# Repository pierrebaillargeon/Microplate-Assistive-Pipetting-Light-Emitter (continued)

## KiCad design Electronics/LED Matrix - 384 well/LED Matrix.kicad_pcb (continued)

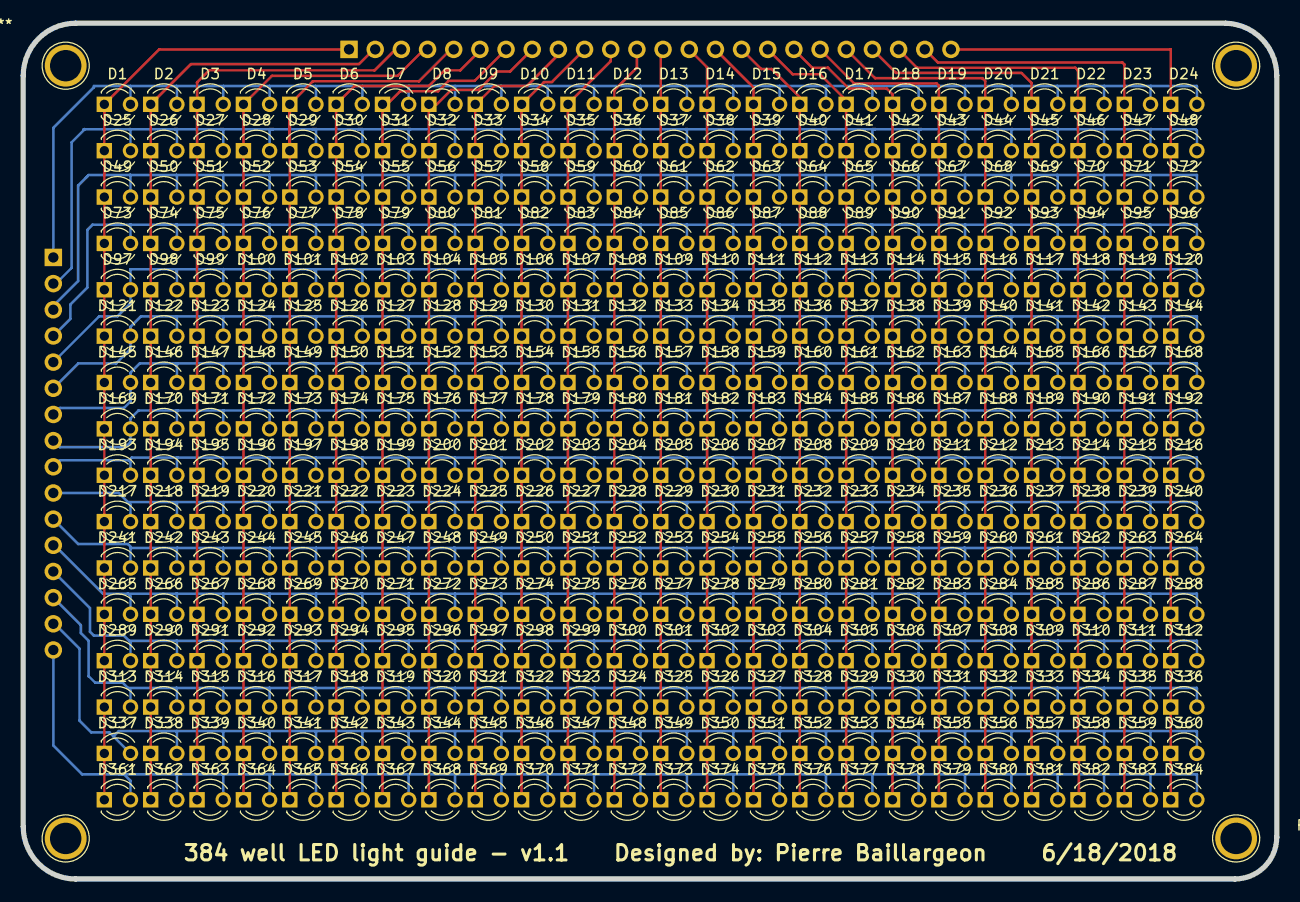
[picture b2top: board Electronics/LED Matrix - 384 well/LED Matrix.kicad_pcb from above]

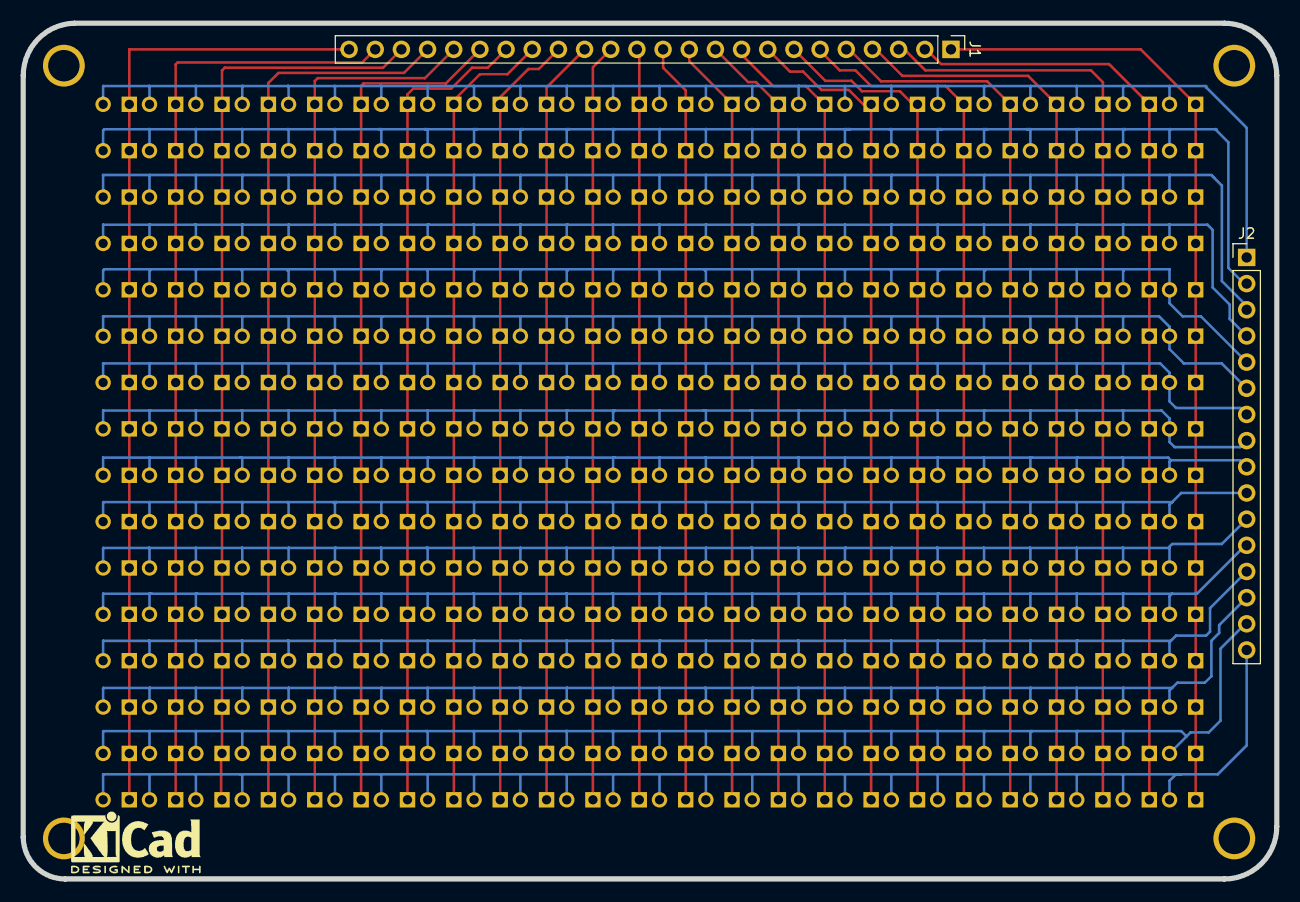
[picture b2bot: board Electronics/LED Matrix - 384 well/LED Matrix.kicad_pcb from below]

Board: 2 copper layers, 121.7 x 83.1 mm, 386 parts (2 on the bottom side), 40 nets.

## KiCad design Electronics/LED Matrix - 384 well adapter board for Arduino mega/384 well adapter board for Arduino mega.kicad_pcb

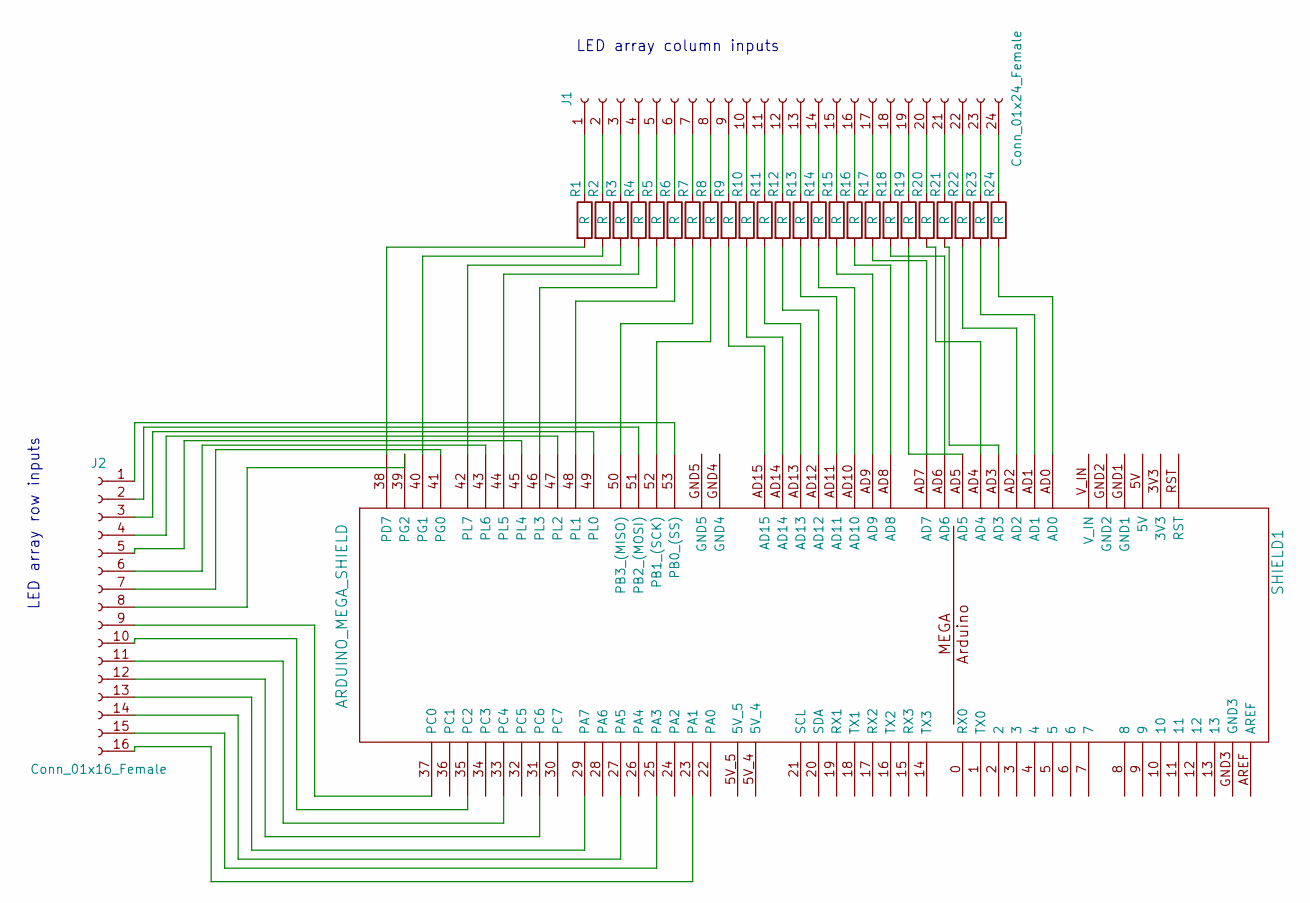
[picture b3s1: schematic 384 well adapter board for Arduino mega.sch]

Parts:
J1: Conn_01x24_Female; Socket_Strip_Straight_1x24_Pitch2.54mm
J2: Conn_01x16_Female; Socket_Strip_Straight_1x16_Pitch2.54mm
R1, R2, R3, R4, R5, R6, R7, R8, R9, R10, R11, R12, R13, R14, R15, R16, R17, R18, R19, R20, R21, R22, R23, R24: R; R_Axial_DIN0207_L6.3mm_D2.5mm_P7.62mm_Horizontal
SHIELD1: ARDUINO_MEGA_SHIELD; ARDUINO MEGA SHIELD

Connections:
unnamed: J1.1, R1.1
unnamed: J1.2, R2.1
unnamed: J1.3, R3.1
unnamed: J1.4, R4.1
unnamed: J1.5, R5.1
unnamed: J1.6, R6.1
unnamed: J1.7, R7.1
unnamed: J1.8, R8.1
unnamed: J1.9, R9.1
unnamed: J1.10, R10.1
unnamed: J1.11, R11.1
unnamed: J1.12, R12.1
unnamed: J1.13, R13.1
unnamed: J1.14, R14.1
unnamed: J1.15, R15.1
unnamed: J1.16, R16.1
unnamed: J1.17, R17.1
unnamed: J1.18, R18.1
unnamed: J1.19, R19.1
unnamed: J1.20, R20.1
unnamed: J1.21, R21.1
unnamed: J1.22, R22.1
unnamed: J1.23, R23.1
unnamed: J1.24, R24.1
unnamed: J2.1, SHIELD1.53 (PB0_(SS))
unnamed: J2.2, SHIELD1.51 (PB2_(MOSI))
unnamed: J2.3, SHIELD1.49 (PL0)
unnamed: J2.4, SHIELD1.47 (PL2)
unnamed: J2.5, SHIELD1.45 (PL4)
unnamed: J2.6, SHIELD1.43 (PL6)
unnamed: J2.7, SHIELD1.41 (PG0)
unnamed: J2.8, SHIELD1.39 (PG2)
unnamed: J2.9, SHIELD1.37 (PC0)
unnamed: J2.10, SHIELD1.35 (PC2)
unnamed: J2.11, SHIELD1.33 (PC4)
unnamed: J2.12, SHIELD1.31 (PC6)
unnamed: J2.13, SHIELD1.29 (PA7)
unnamed: J2.14, SHIELD1.27 (PA5)
unnamed: J2.15, SHIELD1.25 (PA3)
unnamed: J2.16, SHIELD1.23 (PA1)
unnamed: R1.2, SHIELD1.38 (PD7)
unnamed: R2.2, SHIELD1.40 (PG1)
unnamed: R3.2, SHIELD1.42 (PL7)
unnamed: R4.2, SHIELD1.44 (PL5)
unnamed: R5.2, SHIELD1.46 (PL3)
unnamed: R6.2, SHIELD1.48 (PL1)
unnamed: R7.2, SHIELD1.50 (PB3_(MISO))
unnamed: R8.2, SHIELD1.52 (PB1_(SCK))
unnamed: R9.2, SHIELD1.AD15
unnamed: R10.2, SHIELD1.AD14
unnamed: R11.2, SHIELD1.AD13
unnamed: R12.2, SHIELD1.AD12
unnamed: R13.2, SHIELD1.AD11
unnamed: R14.2, SHIELD1.AD10
unnamed: R15.2, SHIELD1.AD9
unnamed: R16.2, SHIELD1.AD8
unnamed: R17.2, SHIELD1.AD7
unnamed: R18.2, SHIELD1.AD6
unnamed: R19.2, SHIELD1.AD5
unnamed: R20.2, SHIELD1.AD4
unnamed: R21.2, SHIELD1.AD3
unnamed: R22.2, SHIELD1.AD2
unnamed: R23.2, SHIELD1.AD1
unnamed: R24.2, SHIELD1.AD0

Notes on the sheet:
LED array column inputs
LED array row inputs

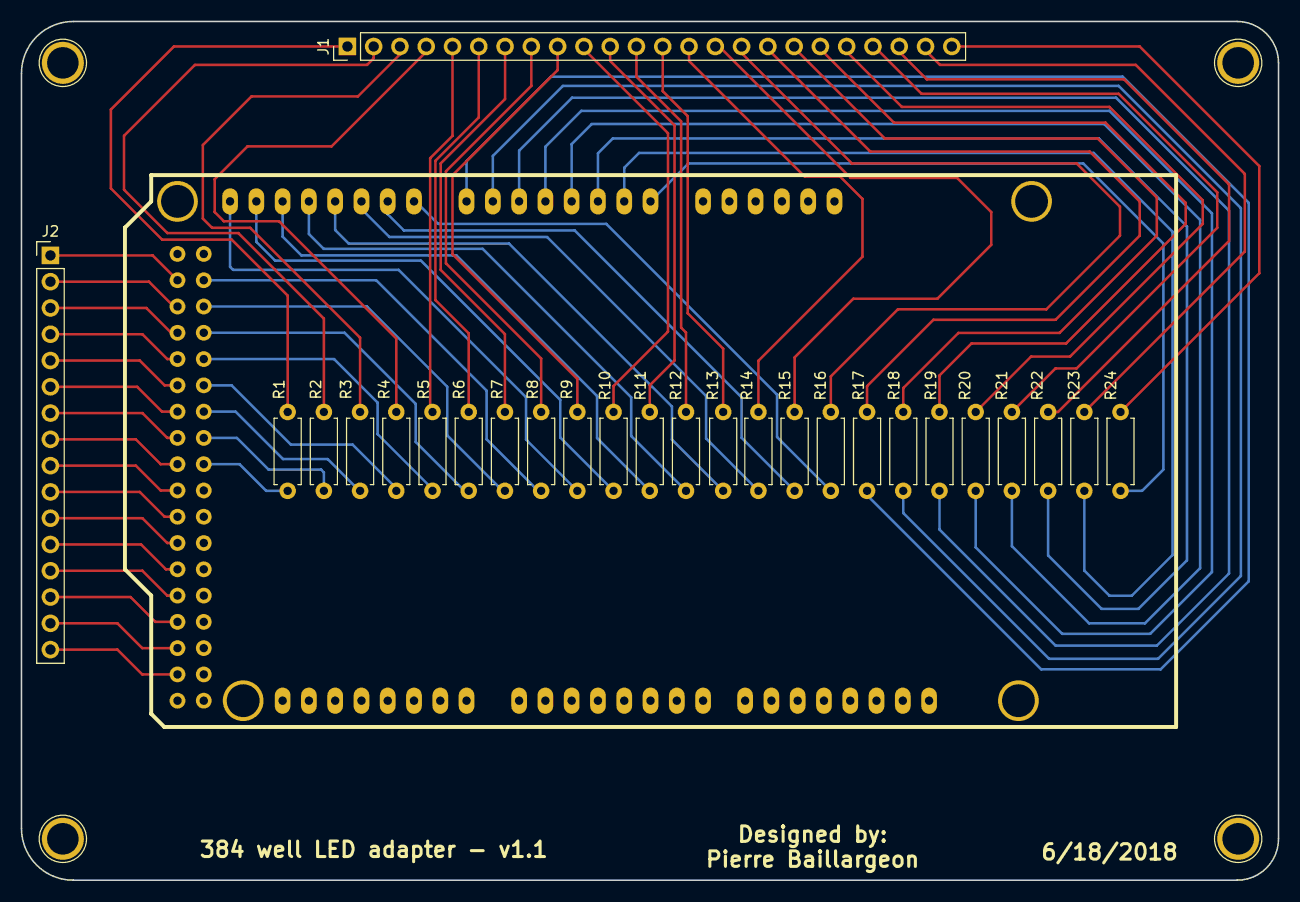
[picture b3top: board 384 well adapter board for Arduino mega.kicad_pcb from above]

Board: 2 copper layers, 121.5 x 83.0 mm, 27 parts (0 on the bottom side), 64 nets.

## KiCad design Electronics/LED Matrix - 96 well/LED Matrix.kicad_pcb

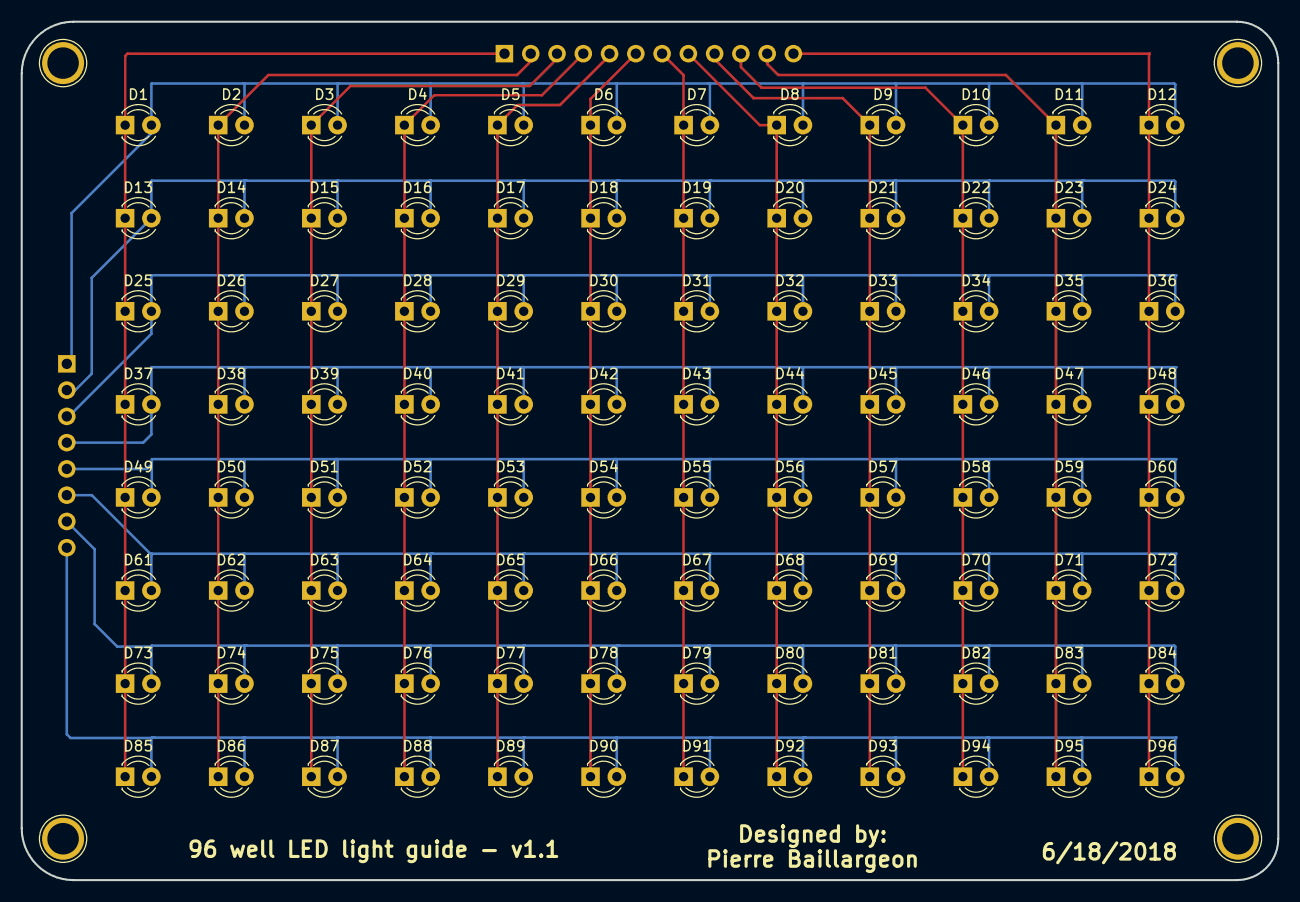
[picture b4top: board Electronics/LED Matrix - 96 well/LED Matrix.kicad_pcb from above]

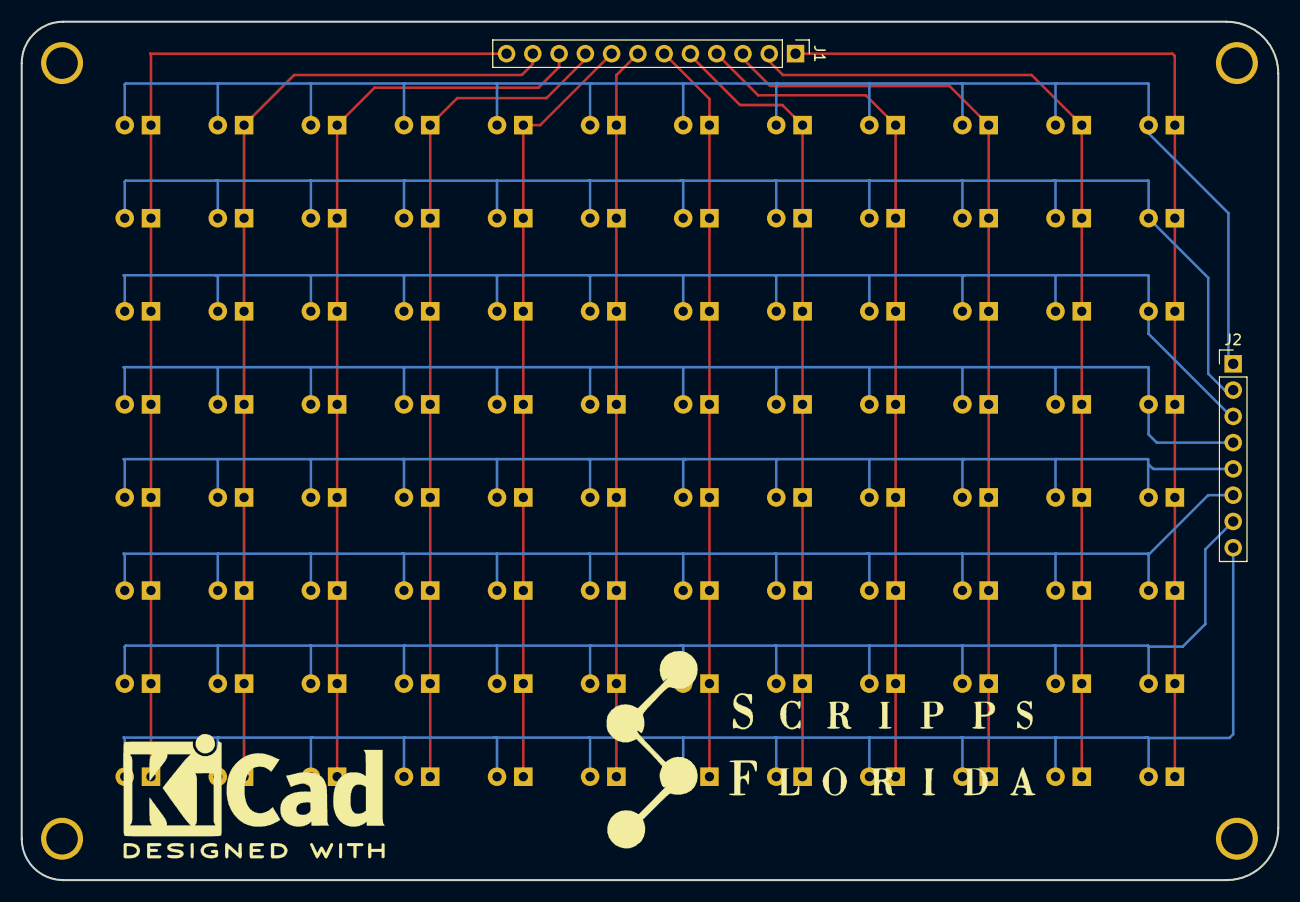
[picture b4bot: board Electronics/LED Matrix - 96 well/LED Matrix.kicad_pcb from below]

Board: 2 copper layers, 121.5 x 83.0 mm, 98 parts (2 on the bottom side), 20 nets.

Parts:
D1, D2, D3, D4, D5, D6, D7, D8, D9, D10, D11, D12, D13, D14, D15, D16, D17, D18, D19, D20, D21, D22, D23, D24, D25, D26, D27, D28, D29, D30, D31, D32, D33, D34, D35, D36, D37, D38, D39, D40, D41, D42, D43, D44, D45, D46, D47, D48, D49, D50, D51, D52, D53, D54, D55, D56, D57, D58, D59, D60, D61, D62, D63, D64, D65, D66, D67, D68, D69, D70, D71, D72, D73, D74, D75, D76, D77, D78, D79, D80, D81, D82, D83, D84, D85, D86, D87, D88, D89, D90, D91, D92, D93, D94, D95, D96: LED; LED_D3.0mm
J1: Conn_01x12_Male; Pin_Header_Straight_1x12_Pitch2.54mm
J2: Conn_01x08_Male; Pin_Header_Straight_1x08_Pitch2.54mm

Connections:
/1: D1.1, D13.1, D25.1, D37.1, D49.1, D61.1, D73.1, D85.1, J1.1
/2: D2.1, D14.1, D26.1, D38.1, D50.1, D62.1, D74.1, D86.1, J1.2
/3: D3.1, D15.1, D27.1, D39.1, D51.1, D63.1, D75.1, D87.1, J1.3
/4: D4.1, D16.1, D28.1, D40.1, D52.1, D64.1, D76.1, D88.1, J1.4
/5: D5.1, D17.1, D29.1, D41.1, D53.1, D65.1, D77.1, D89.1, J1.5
/6: D6.1, D18.1, D30.1, D42.1, D54.1, D66.1, D78.1, D90.1, J1.6
/7: D7.1, D19.1, D31.1, D43.1, D55.1, D67.1, D79.1, D91.1, J1.7
/8: D8.1, D20.1, D32.1, D44.1, D56.1, D68.1, D80.1, D92.1, J1.8
/9: D9.1, D21.1, D33.1, D45.1, D57.1, D69.1, D81.1, D93.1, J1.9
/10: D10.1, D22.1, D34.1, D46.1, D58.1, D70.1, D82.1, D94.1, J1.10
/11: D11.1, D23.1, D35.1, D47.1, D59.1, D71.1, D83.1, D95.1, J1.11
/12: D12.1, D24.1, D36.1, D48.1, D60.1, D72.1, D84.1, D96.1, J1.12
/A: D1.2, D2.2, D3.2, D4.2, D5.2, D6.2, D7.2, D8.2, D9.2, D10.2, D11.2, D12.2, J2.1
/B: D13.2, D14.2, D15.2, D16.2, D17.2, D18.2, D19.2, D20.2, D21.2, D22.2, D23.2, D24.2, J2.2
/C: D25.2, D26.2, D27.2, D28.2, D29.2, D30.2, D31.2, D32.2, D33.2, D34.2, D35.2, D36.2, J2.3
/D: D37.2, D38.2, D39.2, D40.2, D41.2, D42.2, D43.2, D44.2, D45.2, D46.2, D47.2, D48.2, J2.4
/E: D49.2, D50.2, D51.2, D52.2, D53.2, D54.2, D55.2, D56.2, D57.2, D58.2, D59.2, D60.2, J2.5
/F: D61.2, D62.2, D63.2, D64.2, D65.2, D66.2, D67.2, D68.2, D69.2, D70.2, D71.2, D72.2, J2.6
/G: D73.2, D74.2, D75.2, D76.2, D77.2, D78.2, D79.2, D80.2, D81.2, D82.2, D83.2, D84.2, J2.7
/H: D85.2, D86.2, D87.2, D88.2, D89.2, D90.2, D91.2, D92.2, D93.2, D94.2, D95.2, D96.2, J2.8

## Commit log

2018-11-01 Initial commit
    Initial commit
2018-11-09 Update M.A.P.L.E.-Logo.png
    Project logo
2018-11-12 Adding Neopixel based designs to repository
2019-03-26 Added fiducials and cleaned up silkscreen layer
    Added fiducial marks to four corners of board as recommended here: http://www.ladyada.net/library/pcb/fiducials.html
    Also cleaned up the silkscreen layer to properly identify pin 1 of each LED and clean up overlapping text.
2019-03-26 Corrected error on silkscreen
    Location for identification text for C58 was not updated in prior update. It is corrected now.
2019-03-26 Updated C58 reference on silkscreen
    Missed C58 reference correction on previous update. It is now in the correct location.
2019-04-05 Update readme
    Added sample images of 96 and 384 well RGB light guide illumination panels
2019-05-19 Updated to v1.3
    Updated to v1.3. Changes:
    - Removed HCC Module footprint from back to simplify design
    - Added copper pour to front of PCB for +5V
    - Added fiducials for pick and place automation support
2019-05-19 Updated to v1.1
    Updated to v1.1. Changes:
    - Removed HCC module footprint from back to simplify design
    - Added copper pour to front of PCB for +5V
    - Added fiducuals for pick and place automation
2019-06-01 Adding updated photo of v1.3 PCB
    Added updated photo of 96 well RGB light guide - v1.3
2019-06-01 Updated Readme
    Updated readme to show latest version of 96 well light guide PCB
2019-06-01 Updated readme
    Fixed image link
2019-06-01 Update readme
    fix double logo listing
2019-06-08 Created example Arduino code for light panel
    This sample code turns all LEDs of the 96 or 384 well light panel on in a repeating sequence of red, green and blue.
2019-06-10 Create 96-well-rgb-light-guide-wiring-example.png
    Added wiring example for 96 well RGB light guide with light panel power board
2019-06-10 Added Fritzing files
    Added Fritzing part files for 96 well RGB light guide and light panel. Also added example wiring diagram for typical 5V microcontroller.
2019-06-24 Updating PCB images for documentation
    New images of 384 and 96 well light guides for better documentation
2019-06-24 Updated sample image of 384 well PCB
    Latest version is example of PCB assembled by Small Batch Assembly
2019-07-02 Create PortableLightGuide.ino
    Initial checkin of portable light guide firmware.
2019-07-09 Added support for 384 well light panel
    Added support for 384 well light panel to existing code; user can switch between 96 or 384 by using the NUM_LEDS variable.
2019-08-29 Initial commit for serial dilution program
    Adding serial dilution sample application to repository.
2019-09-13 Updated for titration example
    Updated 384 well code for titration demo mode.
2019-09-13 Adding support for titration mode GUI applicaiton
    Added functions to support the new titration mode GUI application
2020-02-20 Add requirements
2020-02-20 Make reading of config file safe
2020-02-20 Add sample transfer CSV
2020-02-20 Add test mode
2020-02-20 Downgrade pandas for pandastable compatiblity
2020-02-20 Reformat code in accordance with PEP 8
2020-02-20 Make LightPanelGUI more OOP
2020-02-20 Add utility method for LED lighting
2020-02-20 Define the center frame at construction time
2020-02-20 Define constants in macros
2020-02-20 Stop sending useless data
2020-02-20 Fix file reading
2020-02-20 Add serial utils to avoid code duplication
2020-02-20 Fix errors in Arduino code
2020-02-20 Move duplicated code to SerialUtils
2020-02-20 Make SerialDilution more OOP
2020-02-25 Working LightGuide
2020-02-25 Process entire serial buffer each iteration
2020-02-25 Make row and column methods generic
2020-02-25 Working serial dilution
2020-02-25 Use non-ascii encoding to shorten message
2020-02-26 Add fancy lighting options
2021-08-12 Example CAD file addition
    Adding CAD files for portable enclosure example.
